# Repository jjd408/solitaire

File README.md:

# Solitaire handheld

A pocket solitaire game: a TI MSP430FR2355 microcontroller drives a Sharp LS013B7DH05 memory LCD, runs from
two AA cells through a TPS63900 buck-boost regulator, and is played with 16 push buttons. The memory LCD keeps its
image without refresh, so the board sleeps almost all the time and wakes when a button is pressed.

## What's here

| Folder | Contents |
| --- | --- |
| `hw/` | Hardware design notes: parts, design decisions, open items ([hw/README.md](hw/README.md)). |
| `hw/sol/` | The KiCad 9 project: schematic (passes ERC) and routed PCB (passes DRC). |
| `hw/lib/` | The project's KiCad library (symbols, footprints, 3D models), generated by the scripts beside it ([hw/lib/README.md](hw/lib/README.md)). |
| `hw/case/` | A 3D-printed case generated from the board: front and back shells and button caps, as STL files ([hw/case/README.md](hw/case/README.md)). |
| `hw/ORDERING.md` | How to order the boards (JLCPCB, assembled), the displays and the battery holders. |
| `sw/` | Firmware, in assembly: the plan ([sw/PLAN.md](sw/PLAN.md)), a document per step (`sw/STEP1-skeleton.md` ... `STEP11-bringup.md`) and the NetBeans MSP430 project `sw/sol`, with its tests in `sw/sol/tests`. |
| `docs/datasheets/` | Datasheets for the parts, with text extracts used while building the library. They belong to their vendors (TI, Sharp, Panasonic, Murata, ALPS). |

## Status

- **Firmware: finished in the simulator** (steps 1-10 of the plan). The whole game plays: moves, undo, scoring,
  options and statistics, the game kept through power loss. `sw/sol/tests/run.sh` checks it on the simulator: 39
  tests, including a whole winning game and screen pictures, with what's kept in FRAM compared byte for byte
  against a Python model of the firmware.
- **Board: ready to order.** Schematic and layout pass ERC and DRC; `hw/sol/make_fab.sh` writes the order files.
- **Case: designed**, not yet printed.
- **Next: building it.** Order the boards and displays (`hw/ORDERING.md`), then bring them up
  (`sw/STEP11-bringup.md`).

## Simulator

The firmware can run before the hardware exists, in a copy of PICSimLab with an MSP430FR2355 backend, the
LS013B7DH05 display and a "Solitaire" board wired like `hw/sol`:
[github.com/jjd408/picsimlab-msp430](https://github.com/jjd408/picsimlab-msp430). Clone it into `sim/` to keep
the layout these notes assume:

```sh
git clone https://github.com/jjd408/picsimlab-msp430 sim/picsimlab-msp430
```

## Tools

- KiCad 9 for `hw/sol`; open `hw/sol/sol.kicad_pro`. The library tables use paths relative to the project.
- Python 3 to regenerate the library (`hw/lib/make_symbols.py`, `make_footprints.py`), FreeCAD 1.0 for the 3D
  models (`freecadcmd hw/lib/make_lcd_model.py`, `make_switch_model.py`).
- TI MSP430-GCC (`msp430-elf-gcc -mmcu=msp430fr2355`) for firmware; Apache NetBeans with the MSP430 Assembly
  plugin ([github.com/jjd408/msp430-asm](https://github.com/jjd408/msp430-asm)) to edit, build, run and debug it.
- FreeCAD 1.0 for the case (`hw/case/make_case.sh`).

## Licence

Copyright jjd408 2026.

The hardware design (everything under `hw/`) is licensed under the CERN Open Hardware Licence Version 2,
Strongly Reciprocal (CERN-OHL-S-2.0); see [LICENSE](LICENSE). You may redistribute and modify it under that
licence. It's distributed WITHOUT ANY EXPRESS OR IMPLIED WARRANTY, INCLUDING OF MERCHANTABILITY, SATISFACTORY
QUALITY AND FITNESS FOR A PARTICULAR PURPOSE; see the licence for the applicable conditions.

Source location: <https://github.com/jjd408/solitaire>. As the licence asks, keep this notice and the source
location in any products you make with the design.

The datasheets in `docs/datasheets/` aren't covered: they belong to their vendors (TI, Sharp, Panasonic, Murata,
ALPS) and are included for reference.

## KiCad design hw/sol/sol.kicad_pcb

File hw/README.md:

# Solitaire handheld: hardware

A pocket solitaire game: an MSP430 microcontroller drives a Sharp memory LCD, runs from two AA cells,
and is played with push buttons. The memory LCD holds its image without refresh, so the board spends
almost all of its time asleep and wakes only when a button is pressed.

The schematic and board are in `sol/`; the schematic passes KiCad's ERC and the board its DRC, with the board matching the
schematic. The parts library is in `lib/`.

## Block diagram

```
 2x AA ──► TPS63900 buck-boost ──► 3.0 V rail ──┬──► MSP430FR2355 (MCU)
 (1.8-3.2 V)                                    │       │  SPI + EXTCOMIN + DISP
                                                │       ▼
                                                └──► Sharp LS013B7DH05 memory LCD
                                                        (via 10-pin FPC connector)
 Buttons ──► MSP430 port pins (interrupt on press; wake from sleep)
 Spy-Bi-Wire header ──► MSP430 (programming and debug)
```

## Parts

| Function | Part | Why |
| --- | --- | --- |
| Microcontroller | TI MSP430FR2355TDBT (TSSOP-38) | 32 KB FRAM, 4 KB RAM, 34 GPIO, sleeps at about 1.2 µA (LPM3, 32 kHz crystal running). Free GCC toolchain. |
| Display | Sharp LS013B7DH05, 1.26 in, 144 × 168, monochrome memory LCD | Holds its image at near-zero power, readable in daylight, 3 V supply, framebuffer fits in the MCU's RAM. |
| Display connector | Panasonic AYF531035 (Y5B, 10 contacts, 0.5 mm pitch) | Sharp's first recommendation for this display. Contacts top and bottom, so the FPC can go in either face down. |
| Power | TI TPS63900 buck-boost (WSON-10) | Holds a steady rail as two AA cells run from 3.2 V down to about 1.8 V, with a quiescent current of about 75 nA. |
| Inductor | Murata DFE201612E-2R2M, 2.2 µH, 2.0 × 1.6 × 1.2 mm | On TI's recommended list for the TPS63900. Saturation current 2.4 A, well above the 1 A TI requires at this board's 100 mA current limit (and enough for the 2 A needed if the limit is ever removed); DC resistance 116 mΩ. |
| Regulator capacitors | Murata GRM188R60J106ME47 (10 µF in) and GRM187R60J226ME15 (22 µF out), 6.3 V X5R 0603 | TI's recommended parts and its typical-application values. |
| Display capacitors | Murata GRM188R71C104KA01 (0.1 µF) and 2 × GRM188R71A105KA61 (1 µF), X7R 0603 | Sharp's Figure 9-1: 0.1 µF DISP to VSS, 1 µF VDDA to VSSA, 1 µF VDD to VSS. |
| Regulator configuration | Yageo RC0603FR-07 series, 1%: 20.5 kΩ (CFG1), 511 Ω (CFG2), 13.3 kΩ (CFG3) | Set 3.0 V out and a 100 mA input current limit; see Power below. |
| Battery | 2 × AA in an open holder with a JST-PH lead (e.g. Adafruit #4194) | Cheap, easy to find, and long-lasting at this current draw. |
| Reverse-battery protection | Infineon IRLML6401TRPBF P-channel MOSFET (SOT-23) | Fully on at the cells' lowest 1.8 V, costing about 12 mV; off if the cells go in backwards. See Power below. |
| Buttons | ALPS SKRPACE010 tact switches | Low-profile, easy to source. |
| Programming | 1 × 4, 2.54 mm Spy-Bi-Wire header: 3V0, TEST/SBWTCK, RST/SBWTDIO, GND | Same order as a LaunchPad eZ-FET's 3V3/TST/RST/GND jumpers, so four jumper wires run straight across. Needs a 47 kΩ pull-up on RST/SBWTDIO and at most 1.1 nF from it to GND (1 nF). |

## Design decisions

### Microcontroller: MSP430FR2355

The game needs a framebuffer in RAM, very low sleep current, and enough pins for a display and a set of
buttons. The FR2355's 4 KB of RAM holds the display's 3,024-byte framebuffer with about 1 KB left for the
stack and game state. If that gets tight, the framebuffer can move to FRAM, which writes at RAM-like speed.

ATtiny1607 and ATtiny3226 were considered. The ATtiny1607's 1 KB of RAM can't hold a framebuffer, and the
ATtiny3226 offered no clear advantage.

### Display: Sharp LS013B7DH05

A memory LCD keeps its image with the CPU asleep and draws microamps, which suits a battery game that
spends most of its time waiting for the player.

| Display | Verdict |
| --- | --- |
| **LS013B7DH05**, 144 × 168 | **Chosen.** 3 V, framebuffer fits in RAM. |
| LS013B7DH03, 128 × 128 | Same pinout and supply, fewer pixels, and Mouser lists it as obsolete. |
| LS027B7DH01, 400 × 240 | Needs a 5 V supply and a 12 KB framebuffer, which doesn't fit in RAM. |
| LS013B7DH06 (colour) | Uncertain availability. |
| JDI LPM013M126A (colour) | Uncertain availability. |

What the display needs from the board:

- **EXTCOMIN at 57–66 Hz.** The display needs its common electrode toggled to avoid DC damage to the
  liquid crystal. That's too often to wake the CPU for. Instead, a Timer_B output clocked from the 32 kHz
  ACLK drives the EXTCOMIN pin directly. It keeps running in LPM3 with the CPU asleep. **EXTCOMIN must
  therefore go on a timer output pin**: P2.0/P2.1 (TB1.1/TB1.2) or P5.0/P5.1 (TB2.1/TB2.2). Those leave both
  SPI ports free.
- **Three capacitors at the connector** (Figure 9-1): 0.1 µF from DISP to VSS, and 1 µF each from VDDA to VSSA
  and VDD to VSS.
- **EXTMODE tied high**, to select the EXTCOMIN pin as the COM source rather than a bit in the SPI data.
- **Supply 2.7–3.3 V.** The rail must stay in this window; 3.0 V suits both the display and the MCU.
- **Glass**: 24.68 × 30.0 × 0.745 mm, viewing area 20.88 × 24.36 mm (taller than it is wide).

### Buttons

Discrete buttons are easy to source and need no custom knob or cap, which keeps the case thin. The display
uses only 5 of the FR2355's 34 GPIO, so there are plenty to spare.

All four ports (P1–P4) have pin interrupts that wake the MCU from every low-power mode, including
LPMx.5, so buttons can go on any of them. The schematic has 16: nine for the stacks (P1.0–P1.6, P2.0–P2.1),
four for the suits (P2.2–P2.5) and three more on P3.0–P3.2. Stacks 1–7 are the tableau's columns; stacks 8
and 9 (SW11, SW12) are the waste and the stock, and sit in the bottom row with SW1–SW3. Each switches to GND, using the MCU's internal
pull-ups.

### Power

Two AA cells feed the TPS63900, which bucks or boosts to a fixed 3.0 V rail across the cells' whole
discharge range.

The inductor must be 2.2 µH. TI recommends five: Coilcraft XFL4020-222ME, Bourns SRN3015TA-2R2M, and Murata
DFE252010F-2R2M, DFE201612E-2R2M and DFE201210U-2R2M. The DFE201612E is the smallest with margin; the
2.0 × 1.2 mm DFE201210U saturates at exactly TI's 2 A minimum, without the 20% headroom TI recommends. If
efficiency at heavier loads ever matters more than board space, the DFE252010F (2.5 × 2.0 × 1.0 mm, 97 mΩ) is
the swap; at this board's few-milliamp load the difference is small.

The regulator reads three resistors to ground once at power-up (Tables 7-2 and 7-3 of TI's datasheet):

| Pin | Resistor | Sets |
| --- | --- | --- |
| CFG1 | 20.5 kΩ | 3.0 V output when SEL is high |
| CFG2 | 511 Ω | 100 mA input current limit |
| CFG3 | 13.3 kΩ | 3.0 V output when SEL is low |

Both output settings are 3.0 V, so SEL's level doesn't matter; it's tied to VIN, like EN. Neither pin may be
left open. The 100 mA limit still allows about 50 mA out with nearly flat cells at 1.8 V, far more than the
board draws, and limits the input to about 26 mA if the output is shorted. Use resistors of 1% or better and
200 ppm/°C or better, keep the CFG traces short, and put no capacitance on them (10 pF maximum).

There's no power switch: the board is always on and relies on sleep. When programming, don't connect the
debugger's 3.3 V while the batteries are in, or it will fight the regulator's output: either remove the batteries
and let the debugger power the board (3.3 V is within the MCU's and display's limits), or leave its 3V3 wire off.

**Reverse-battery protection.** The TPS63900 isn't protected against reversed cells, so Q1, a P-channel MOSFET
(Infineon IRLML6401TRPBF, SOT-23), sits in the positive lead between the battery pad (BATT_IN) and VBAT, its
drain to the battery, source to VBAT, gate to GND. With the cells the right way round, its body diode starts
the rail and the gate, 1.8–3.2 V below the source, turns it fully on: 125 mΩ at most at the cells' 1.8 V end,
12 mV at the 100 mA input limit. Reversed, the gate is above the source and the body diode is backwards, so
nothing conducts. It draws no current of its own. A series diode would cost 0.2–0.3 V, too much at 1.8 V; the
IRLML6401 is one of the few small P-MOSFETs rated at a gate drive this low (its threshold is −0.4 to −0.95 V).
Other makers sell parts named IRLML6401 with different ratings: order Infineon's.

### Display connector and FPC routing

The AYF531035 has contacts on both sides, so the FPC can go in either face down:

- **Display face up, FPC straight into the connector** (FPC contacts facing the board): FPC lead 1 meets
  connector pad 1. The library's symbol and footprint assume this.
- **FPC bent back so the display sits over the connector**: the leads reverse (lead 1 meets pad 10), and the
  schematic's pin numbers must be swapped.

Sharp's limits on the FPC: bend only 0.8–6.0 mm from the glass edge, inner radius at least 0.45 mm, never
toward the display face, and no more than three bends.

## Board

A two-layer, 1.6 mm board, 64 × 80 mm with 3 mm corner radii and an M2 mounting hole 3.5 mm in from each corner. Every
part is on the front:

```
+----------------------------------------------------------------+
|  o   2xAA        +------------------------+               o    |
|      + -         |                        |                    |
|                  |   LS013B7DH05 glass    |                    |
|  R1-3 U2 L1      |                        |                    |
|       C1 C2      |                        |                    |
|                  +----+    FPC     +------+                    |
|                       |            |  C8 C6 U1  R4 C7  J3 SBW  |
|                 C4 C3 [ connector  ] C5                        |
|          [S1]     [S2]      [S3]      [S4]           suits     |
|       [1]  [2]  [3]  [4]  [5]  [6]  [7]               stacks   |
|  o  [STOCK] [WASTE] [NEW] [UNDO] [OPTIONS]                 o   |
+----------------------------------------------------------------+
```

- **Display.** The glass lies face up at the top, centred, on a thin layer of tape; its FPC runs straight down
  into the connector, which is turned to face it (the library's lead-1-to-pad-1 orientation). The board-only
  footprint `LCD1` (`lib/`'s `LCD_Sharp_LS013B7DH05_Outline`) marks where the glass and FPC lie, keeps parts out
  from under them, and carries the display's 3D model; silkscreen corner marks line the glass up. Tracks and
  tented vias do run under the glass. The FPC's end is taken to go 2.63 mm past the connector's pad row, which
  puts the glass's bottom edge 11.0 mm above it; the case should allow ±0.5 mm there.
- **Buttons** follow the simulator's Solitaire board: suits S1–S4 (SW13–16) on a 9.75 mm pitch, the seven
  tableau stacks (SW4–10) on 6.5 mm, then a bottom row on 9.75 mm: stock (SW12), waste (SW11), new game (SW1),
  undo (SW2) and options (SW3), stock and waste at the left as they are on the screen. Each is labelled on the
  silkscreen with its number or job.
- **MCU** right of the connector, so its SCS/SI/SCLK pins face the connector's signal pads; C6 and C8 by DVCC.
- **Power** left of the display: the battery pads (TP1 +, TP2 −) for the holder's leads, then the TPS63900 with
  L1 straight across from its LX pins, C1 at VIN, C2 under VOUT and the CFG resistors beside their pins.
- **Programming**: the Spy-Bi-Wire header on the right edge, its pins labelled, with R4 and C7 beside it.

Rules: 0.2 mm tracks and clearance (0.3 mm for the supply, battery, inductor and ground nets, narrowing to 0.2 mm
at fine-pitch pads), 0.6/0.3 mm vias, copper 0.5 mm from the edge. The TPS63900 footprint's thermal vias are
0.2 mm drills, so the minimum hole is 0.2 mm (standard at JLCPCB and most others). Both layers are poured with
ground; the back is kept mostly unbroken and stitched to the front with vias about every 4 mm. Reference
designators are on the fabrication layer, so the silkscreen carries only labels.

The board is made by two scripts in `sol/`, run with KiCad's Python from that folder:

- `python3 layout.py` places everything: outline, holes, the display outline, parts, labels, and the net
  classes and rules in `sol.kicad_pro`.
- `python3 route.py` routes it (about 15 minutes) with a small negotiated-congestion maze router on a 0.1 mm grid,
  fans out every ground pad to a via, stitches and pours ground, and fills the zones. The MCU's decoupling
  capacitors' ground pads are routed to its DVSS pin like a signal, so the other tracks can't wall them off from
  the pour; a last check walks the ground net and joins any pad still cut off.

Both start over from the board's footprints, so edit `PLACE` in `layout.py` and rerun them rather than editing
the routed board by hand (or, once you do edit it by hand, stop rerunning them). Check the result with
`kicad-cli pcb drc --schematic-parity sol.kicad_pcb`.

## Files

- `lib/`: KiCad 9 symbols, footprints and 3D models for the parts above; see `lib/README.md`. Everything there is
  generated by scripts, so edit the scripts and rerun them.
- `../docs/datasheets/`: datasheets for the MCU, regulator, displays and connector.

Firmware toolchain: TI MSP430-GCC 9.3.1.11 at `~/ti/msp430-gcc` (`-mmcu=msp430fr2355`). The mspdebug source is in
`~/ti/src/mspdebug` but isn't built yet; it needs `libusb-dev` and `libreadline-dev`.

## Ordering

`sh sol/make_fab.sh` checks the board (DRC with schematic parity) and writes `sol/fab/`: Gerbers and Excellon drill
files (zipped as `sol-gerbers.zip`), the BOM (`sol-bom.csv`: manufacturer and part number for every part), the
placement file (`sol-cpl.csv`) and an assembly drawing (`sol-assembly.pdf`, the parts' references). Coordinates are
from the board's bottom-left corner. `fab/` isn't kept in git: rerun the script after any change.

For the board house: 2 layers, 1.6 mm FR-4, 1 oz copper, ENIG finish (flat pads for the 0.5 mm-pitch WSON and FPC
connector), 64 × 80 mm. Tracks and gaps are 0.2 mm at the least; the smallest holes are the TPS63900 footprint's
0.2 mm thermal vias (the board's own vias are 0.3 mm). Bought separately: the display (LS013B7DH05, it plugs into
DS1, the AYF531035) and the battery holder. J3, the programming header, is marked do-not-populate (the case has
no room for it): its plated holes are drilled, and a header or pogo pins pressed into them from the back program
the board, so every fitted part is surface-mount.

### Ordering from JLCPCB (2 assembled boards)

The full ordering guide, with the displays, battery holders and a budget, is in [ORDERING.md](ORDERING.md).

The schematic's LCSC field holds each part's JLCPCB/LCSC number, so `make_fab.sh` also writes `jlc-bom.csv` and
`jlc-cpl.csv` in JLCPCB's format. On jlcpcb.com:

1. Upload `fab/sol-gerbers.zip`. Board: 2 layers, 1.6 mm, quantity 5 (the minimum), surface finish **ENIG**.
2. Turn on PCB Assembly: Economic, top side, **quantity 2** (the other 3 boards come bare).
3. Upload `fab/jlc-bom.csv` and `fab/jlc-cpl.csv`. Check every part was matched and is in stock: the MCU (C2053375)
   and the connector (C425133) are the ones to watch. A part that's out can be bought through JLCPCB's global
   sourcing or pre-ordered into its parts store, at the cost of some days.
4. **Check each part's rotation in the 3D preview** and rotate any that are wrong: JLCPCB's footprints don't always
   share KiCad's zero, typically for U1, U2, Q1, L1, DS1 and the switches. Pin 1 marks: U1's and U2's dots, DS1's
   chamfered corner on the assembly drawing.
5. J3 isn't in the BOM or placement file (do-not-populate), so the order is all surface-mount.

Not from JLCPCB: the displays (LS013B7DH05, Mouser or DigiKey) and the battery holders.

Substitutions in the BOM, each equal or better than the original part: C2 is GRM188R60J226ME15D (TI's list names
GRM187R60J226ME15, which isn't sold); C5 and C6 are GCJ188R71C104KA01D (GRM188R71C104KA01 is obsolete); R3 is
the thin-film RT0603FRE0713K3L (1%, 50 ppm/°C: the thick-film RC part isn't stocked). The MCU's LCSC listing is
the reel packaging, MSP430FR2355TDBTR, the same chip.

Reviewed before ordering (2026-11-14):
- **The TPS63900 against TI's layout guidelines** (datasheet section 10): the input and output capacitors are
  within 2 mm of their pins, all the regulator's tracks are on the top layer and at most about 1.5 mm, and the
  capacitors' ground pads, the GND pin and the thermal pad share the top-layer ground pour. They now join it
  solidly rather than through thermal-relief spokes (`route.py`'s `SOLID_GROUND`), keeping the loops short and
  wide as TI asks.
- **The AYF531035 footprint against Panasonic's recommended pattern** (Y5B datasheet, page 7): the pads, pitch
  and hold-down pads match. The signal pads' solder paste now follows Panasonic's stencil pattern, 0.25 × 0.55 mm
  for a 120 µm stencil, against bridging at 0.5 mm pitch.
- **The BOM:** every part has its manufacturer and part number (the switches' button names moved to a separate
  Function field), and the battery pads are left off it.

## Open items

- Order: JLCPCB, 2 assembled boards (`ORDERING.md`); check each part's stock and rotation in its preview when
  placing the order.
- Confirm how far the FPC goes into the connector against a sample, and with it the display's position (the case
  window allows ±0.5 mm).
- Print the case (`case/`, made by `case/make_case.sh`) and check its fit: one cap and the front first; measure
  the battery holder before printing the back.
- Bring the boards up: `../sw/STEP11-bringup.md`.

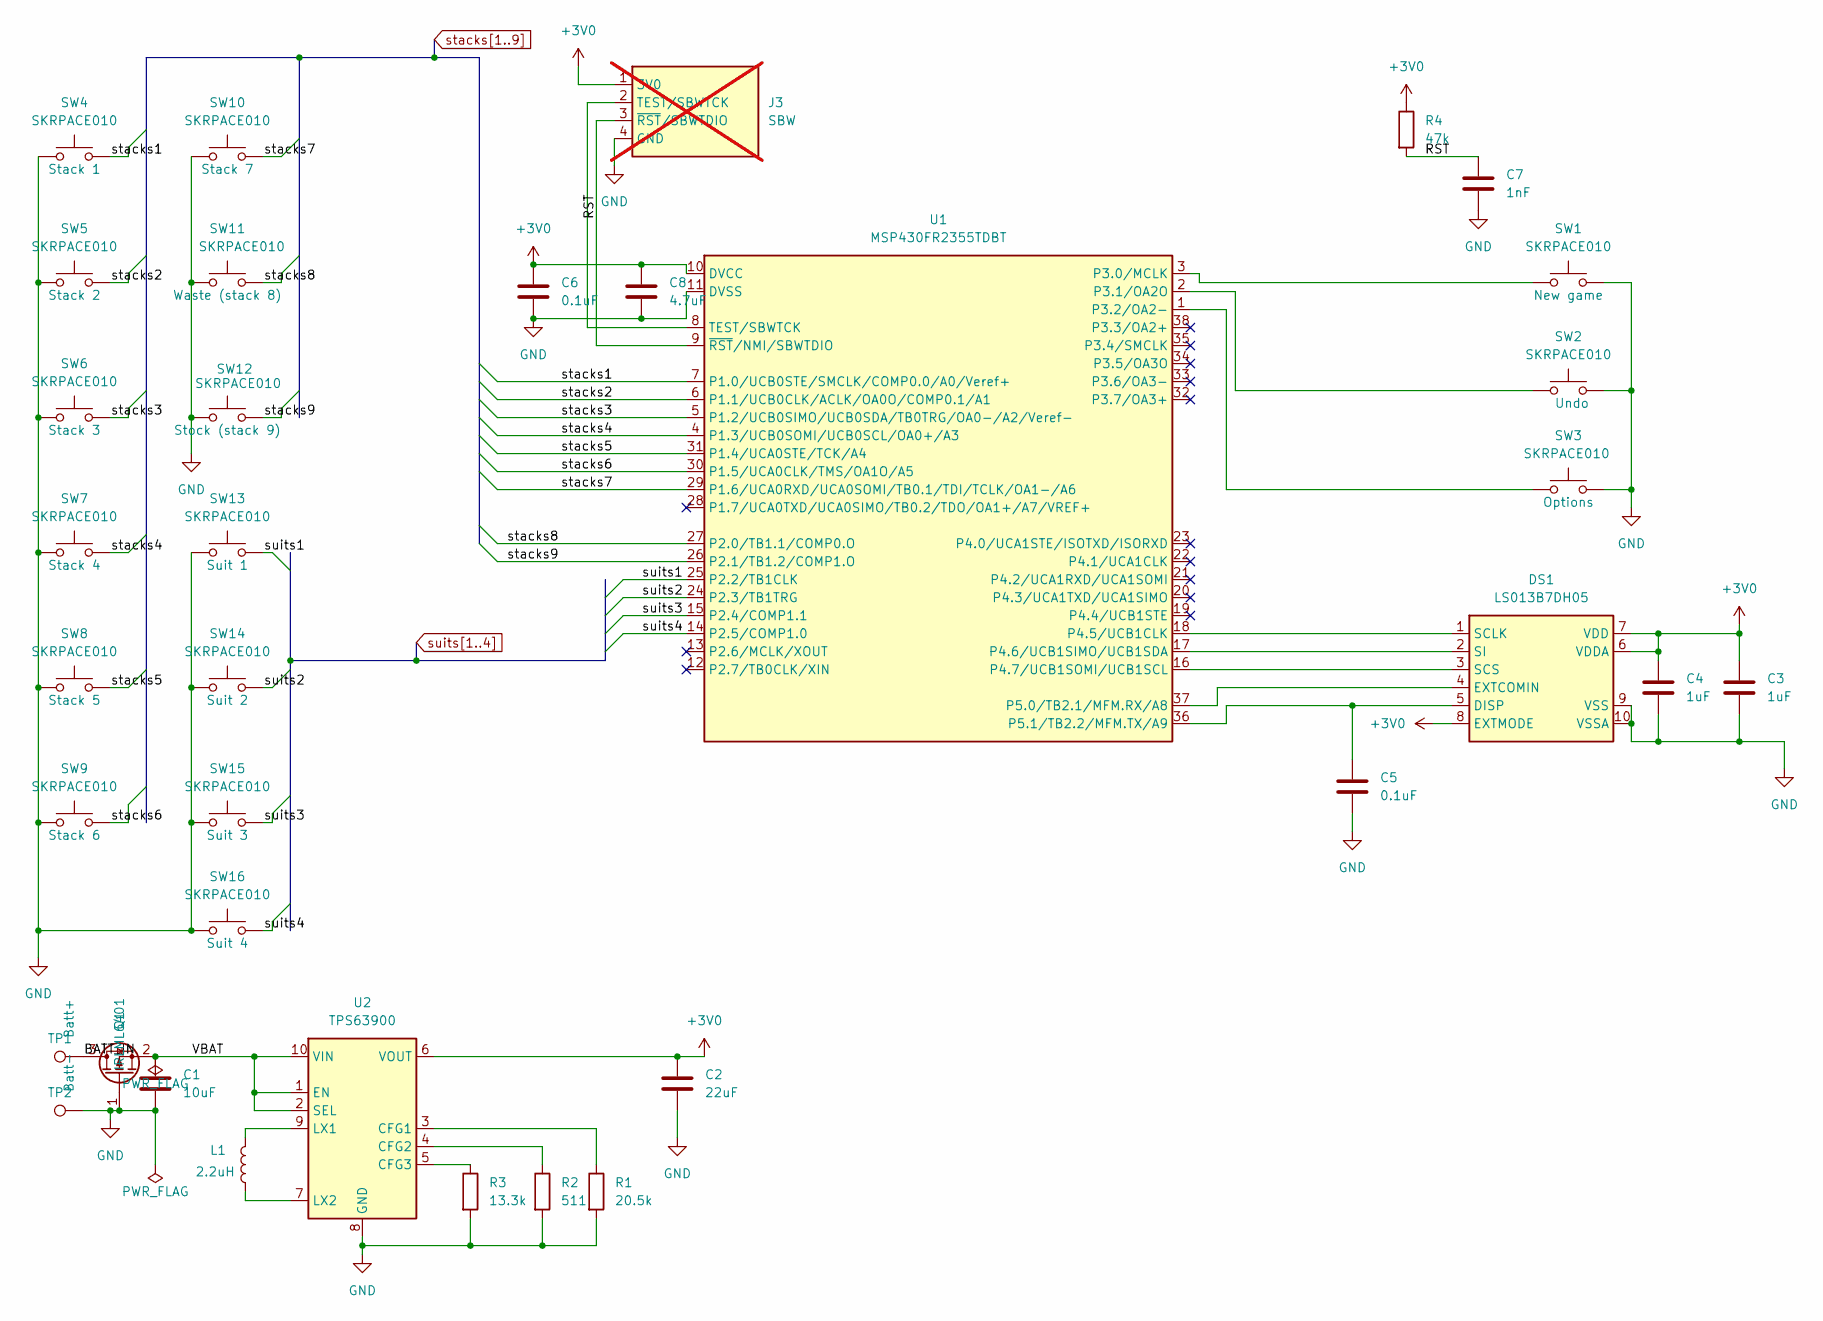
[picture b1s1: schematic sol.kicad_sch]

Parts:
C1: 10uF; C_0603_1608Metric; MPN GRM188R60J106ME47; LCSC C77041
C2: 22uF; C_0603_1608Metric; MPN GRM188R60J226ME15D; LCSC C440187
C3, C4: 1uF; C_0603_1608Metric; MPN GRM188R71A105KA61; LCSC C97888
C5, C6: 0.1uF; C_0603_1608Metric; MPN GCJ188R71C104KA01D; LCSC C710619
C7: 1nF; C_0603_1608Metric; MPN GRM188R71H102KA01; LCSC C71653
C8: 4.7uF; C_0603_1608Metric; MPN GRM188R60J475KE19; LCSC C71631
DS1: LS013B7DH05; Panasonic_AYF531035_1x10-1MP_P0.5mm_Horizontal; MPN AYF531035; LCSC C425133
J3: SBW; PinHeader_1x04_P2.54mm_Vertical; MPN PZ254V-11-04P; LCSC C492403; not fitted
L1: 2.2uH; L_Murata_DFE201612E; MPN DFE201612E-2R2M=P2; LCSC C337893
Q1: IRLML6401; SOT-23; MPN IRLML6401TRPBF; LCSC C3034
R1: 20.5k; R_0603_1608Metric; MPN RC0603FR-0720K5L; LCSC C273789
R2: 511; R_0603_1608Metric; MPN RC0603FR-07511RL; LCSC C137703
R3: 13.3k; R_0603_1608Metric; MPN RT0603FRE0713K3L; LCSC C863573
R4: 47k; R_0603_1608Metric; MPN RC0603FR-0747KL; LCSC C105579
SW1, SW2, SW3, SW4, SW5, SW6, SW7, SW8, SW9, SW10, SW11, SW12, SW13, SW14, SW15, SW16: SKRPACE010; SW_Alps_SKRPACE010; MPN SKRPACE010; LCSC C139797
TP1: Batt+; TestPoint_THTPad_2.0x2.0mm_Drill1.0mm
TP2: Batt-; TestPoint_THTPad_2.0x2.0mm_Drill1.0mm
U1: MSP430FR2355TDBT; TSSOP-38_4.4x9.7mm_P0.5mm; MPN MSP430FR2355TDBT; LCSC C2053375
U2: TPS63900; WSON-10-1EP_2.5x2.5mm_P0.5mm_EP1.2x2mm_ThermalVias; MPN TPS63900DSKR; LCSC C1518762

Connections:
+3V0: C2.1, C3.1, C4.1, C6.1, C8.1, DS1.6 (VDDA), DS1.7 (VDD), DS1.8 (EXTMODE), J3.1 (3V0), R4.1, U1.10 (DVCC), U2.6 (VOUT)
/BATT_IN: Q1.3 (D), TP1.1
/RST: C7.1, J3.3 (~RST/SBWTDIO), R4.2, U1.9 (~RST/NMI/SBWTDIO)
/VBAT: C1.1, Q1.2 (S), U2.1 (EN), U2.2 (SEL), U2.10 (VIN)
GND: C1.2, C2.2, C3.2, C4.2, C5.2, C6.2, C7.2, C8.2, DS1.9 (VSS), DS1.10 (VSSA), J3.4 (GND), Q1.1 (G), R1.2, R2.2, R3.2, SW1.2, SW2.2, SW3.2, SW4.1, SW5.1, SW6.1, SW7.1, SW8.1, SW9.1, SW10.1, SW11.1, SW12.1, SW13.1, SW14.1, SW15.1, SW16.1, TP2.1, U1.11 (DVSS), U2.8 (GND), U2.11 (GND)
unnamed: C5.1, DS1.5 (DISP), U1.36 (P5.1/TB2.2/MFM.TX/A9)
unnamed: DS1.4 (EXTCOMIN), U1.37 (P5.0/TB2.1/MFM.RX/A8)
unnamed: DS1.1 (SCLK), U1.18 (P4.5/UCB1CLK)
unnamed: DS1.3 (SCS), U1.16 (P4.7/UCB1SOMI/UCB1SCL)
unnamed: DS1.2 (SI), U1.17 (P4.6/UCB1SIMO/UCB1SDA)
unnamed: J3.2 (TEST/SBWTCK), U1.8 (TEST/SBWTCK)
unnamed: SW1.1, U1.3 (P3.0/MCLK)
unnamed: SW2.1, U1.2 (P3.1/OA2O)
unnamed: SW3.1, U1.1 (P3.2/OA2-)
unnamed: R1.1, U2.3 (CFG1)
unnamed: R2.1, U2.4 (CFG2)
unnamed: R3.1, U2.5 (CFG3)
unnamed: L1.2, U2.9 (LX1)
unnamed: L1.1, U2.7 (LX2)
stacks1: SW4.2, U1.7 (P1.0/UCB0STE/SMCLK/COMP0.0/A0/Veref+)
stacks2: SW5.2, U1.6 (P1.1/UCB0CLK/ACLK/OA0O/COMP0.1/A1)
stacks3: SW6.2, U1.5 (P1.2/UCB0SIMO/UCB0SDA/TB0TRG/OA0-/A2/Ve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)
stacks4: SW7.2, U1.4 (P1.3/UCB0SOMI/UCB0SCL/OA0+/A3)
stacks5: SW8.2, U1.31 (P1.4/UCA0STE/TCK/A4)
stacks6: SW9.2, U1.30 (P1.5/UCA0CLK/TMS/OA1O/A5)
stacks7: SW10.2, U1.29 (P1.6/UCA0RXD/UCA0SOMI/TB0.1/TDI/TCLK/OA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)
stacks8: SW11.2, U1.27 (P2.0/TB1.1/COMP0.O)
stacks9: SW12.2, U1.26 (P2.1/TB1.2/COMP1.O)
suits1: SW13.2, U1.25 (P2.2/TB1CLK)
suits2: SW14.2, U1.24 (P2.3/TB1TRG)
suits3: SW15.2, U1.15 (P2.4/COMP1.1)
suits4: SW16.2, U1.14 (P2.5/COMP1.0)

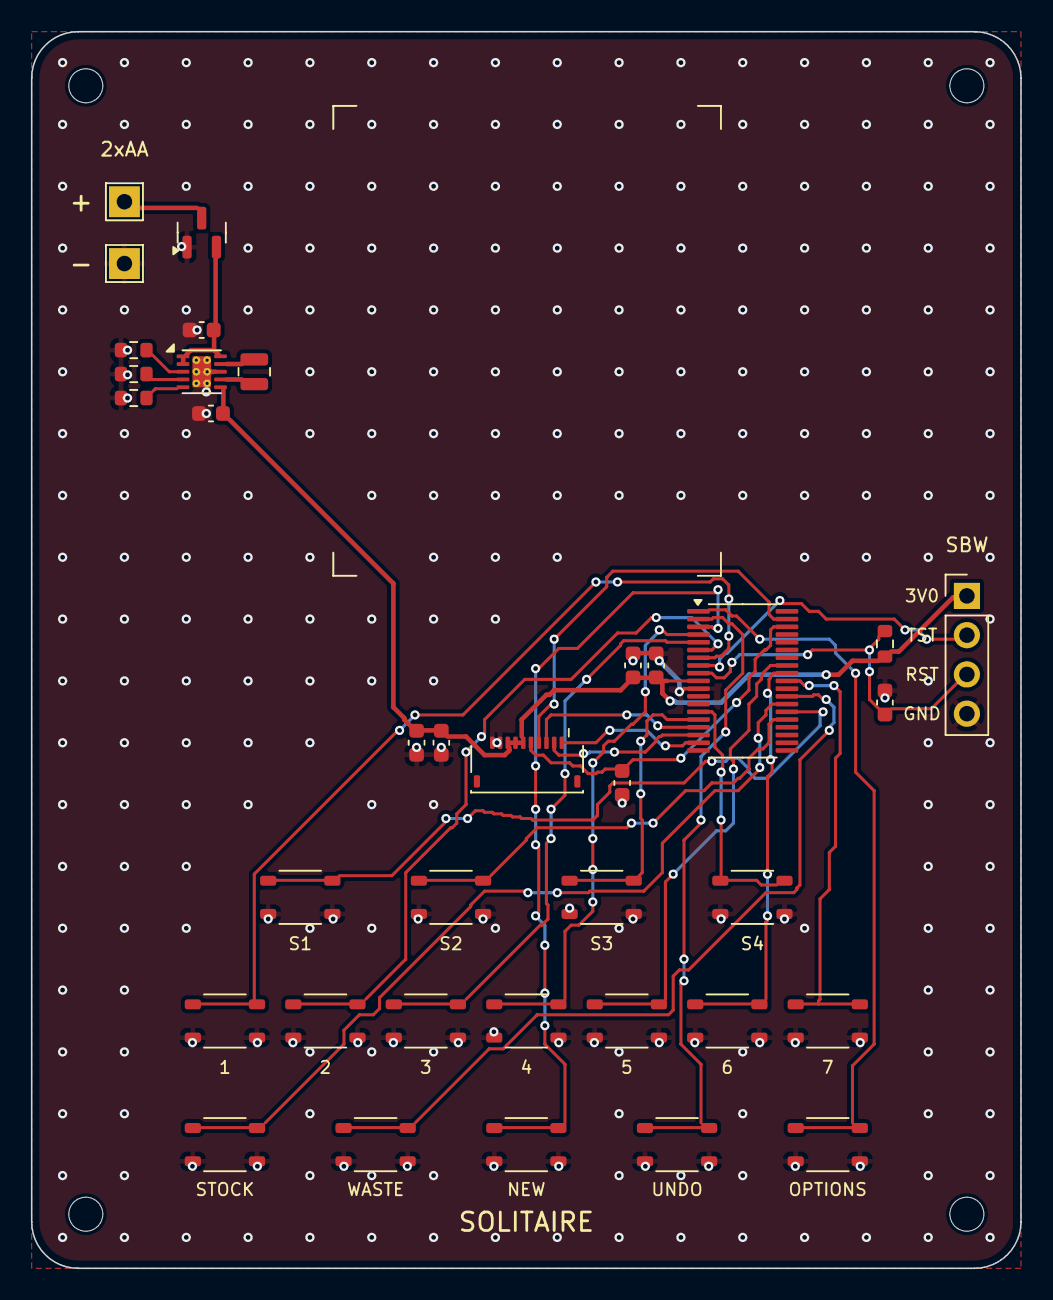
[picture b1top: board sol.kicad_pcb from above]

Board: 2 copper layers, 64.0 x 80.0 mm, 41 parts (0 on the bottom side), 32 nets.

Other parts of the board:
H1, H2, H3, H4: MountingHole_2.2mm_M2
LCD1: LS013B7DH05; LCD_Sharp_LS013B7DH05_Outline

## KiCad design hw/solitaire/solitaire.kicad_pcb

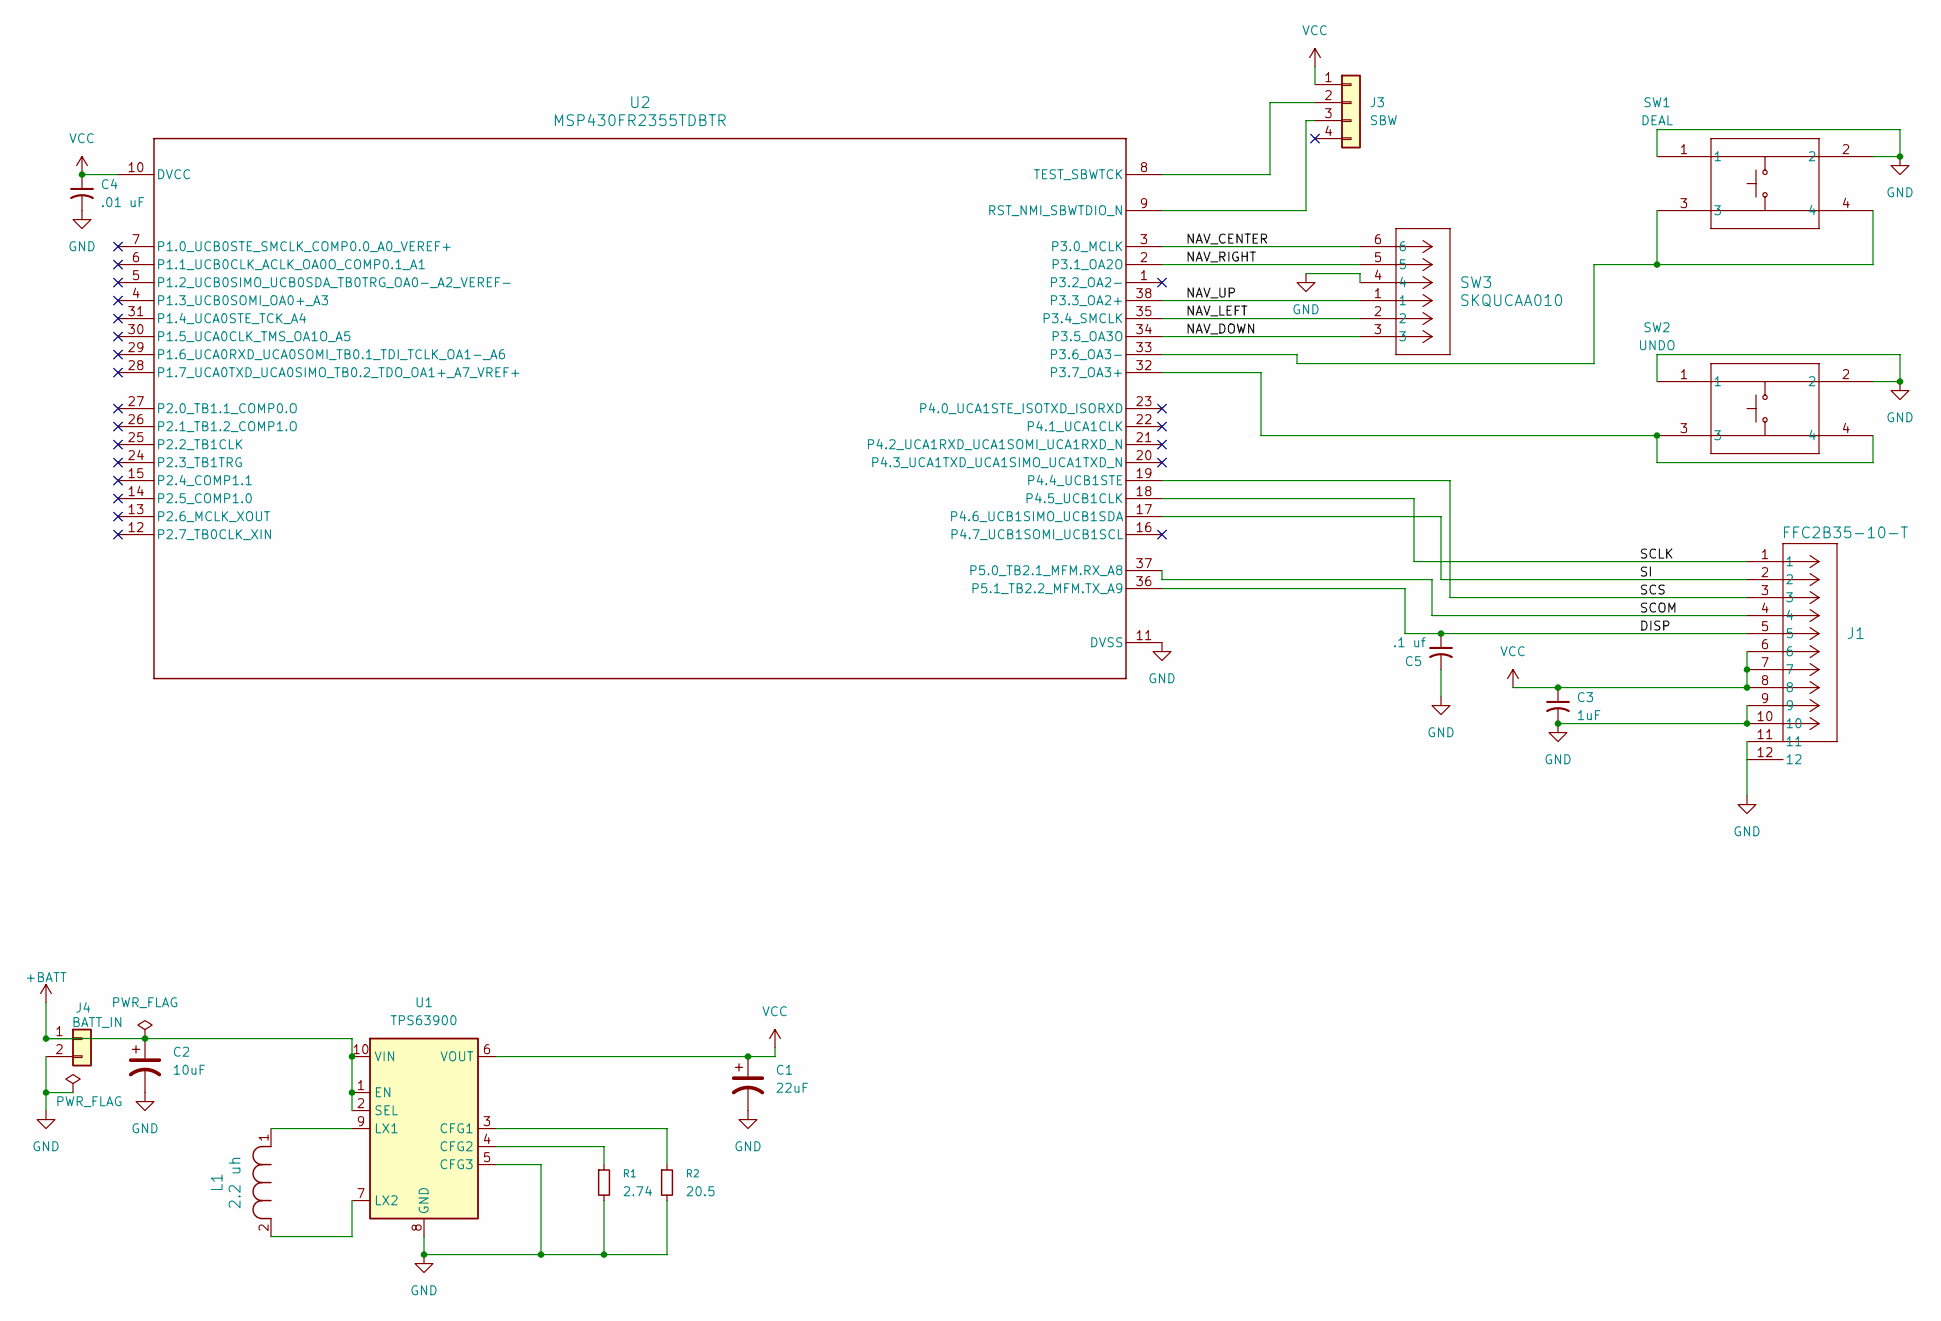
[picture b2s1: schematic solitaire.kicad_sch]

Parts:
C1: 22uF; C_0603_1608Metric
C2: 10uF; C_0603_1608Metric
C3: 1uF; C_0603_1608Metric
C4: .01 uF; C_0603_1608Metric
C5: .1 uf; C_0603_1608Metric
J1: FFC2B35-10-T; CONN_FFC2B35-10-x_GCT
J3: SBW; PinHeader_1x04_P2.54mm_Vertical
J4: BATT_IN; JST_PH_S2B-PH-K_1x02_P2.00mm_Horizontal
L1: 2.2 uh; IND_DFE2016_MUR
R1: 2.74; R_0603_1608Metric
R2: 20.5; R_0603_1608Metric
SW1: DEAL; SW_SKRPACE010_AAL
SW2: UNDO; SW_SKRPACE010_AAL
SW3: SKQUCAA010; CONN_SKQUC_ALPS
U1: TPS63900; WSON-10-1EP_2.5x2.5mm_P0.5mm_EP1.2x2mm_ThermalVias
U2: MSP430FR2355TDBTR; DBT0038A_L

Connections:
+BATT: C2.1, J4.1, U1.1 (EN), U1.2 (SEL), U1.10 (VIN)
/DISP: C5.1, J1.5, U2.36 (P5.1_TB2.2_MFM.TX_A9)
/NAV_CENTER: SW3.6, U2.3 (P3.0_MCLK)
/NAV_DOWN: SW3.3, U2.34 (P3.5_OA3O)
/NAV_LEFT: SW3.2, U2.35 (P3.4_SMCLK)
/NAV_RIGHT: SW3.5, U2.2 (P3.1_OA2O)
/NAV_UP: SW3.1, U2.38 (P3.3_OA2+)
/SCLK: J1.1, U2.18 (P4.5_UCB1CLK)
/SCOM: J1.4, U2.37 (P5.0_TB2.1_MFM.RX_A8)
/SCS: J1.3, U2.19 (P4.4_UCB1STE)
/SI: J1.2, U2.17 (P4.6_UCB1SIMO_UCB1SDA)
GND: C1.2, C2.2, C3.2, C4.2, C5.2, J1.9, J1.10, J1.11, J1.12, J4.2, R1.2, R2.2, SW1.1, SW1.2, SW2.1, SW2.2, SW3.4, U1.5 (CFG3), U1.8 (GND), U1.11 (GND), U2.11 (DVSS)
unnamed: J3.2, U2.8 (TEST_SBWTCK)
unnamed: J3.3, U2.9 (RST_NMI_SBWTDIO_N)
unnamed: R2.1, U1.3 (CFG1)
unnamed: R1.1, U1.4 (CFG2)
unnamed: L1.1, U1.9 (LX1)
unnamed: L1.2, U1.7 (LX2)
unnamed: SW1.3, SW1.4, U2.33 (P3.6_OA3-)
unnamed: SW2.3, SW2.4, U2.32 (P3.7_OA3+)
VCC: C1.1, C3.1, C4.1, J1.6, J1.7, J1.8, J3.1, U1.6 (VOUT), U2.10 (DVCC)

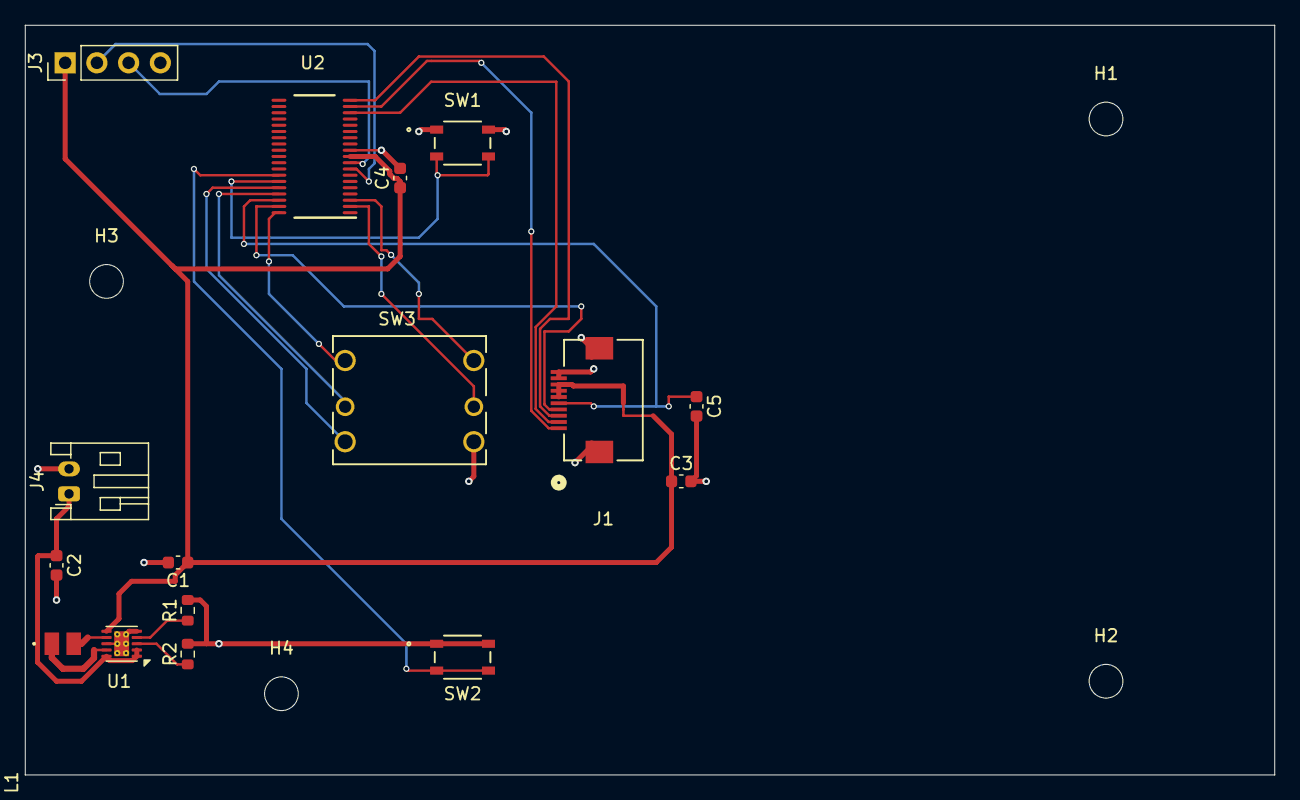
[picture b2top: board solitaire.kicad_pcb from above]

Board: 2 copper layers, 100.0 x 60.0 mm, 20 parts (0 on the bottom side), 21 nets.

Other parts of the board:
H1, H2, H3, H4: MountingHole_2.7mm_M2.5
